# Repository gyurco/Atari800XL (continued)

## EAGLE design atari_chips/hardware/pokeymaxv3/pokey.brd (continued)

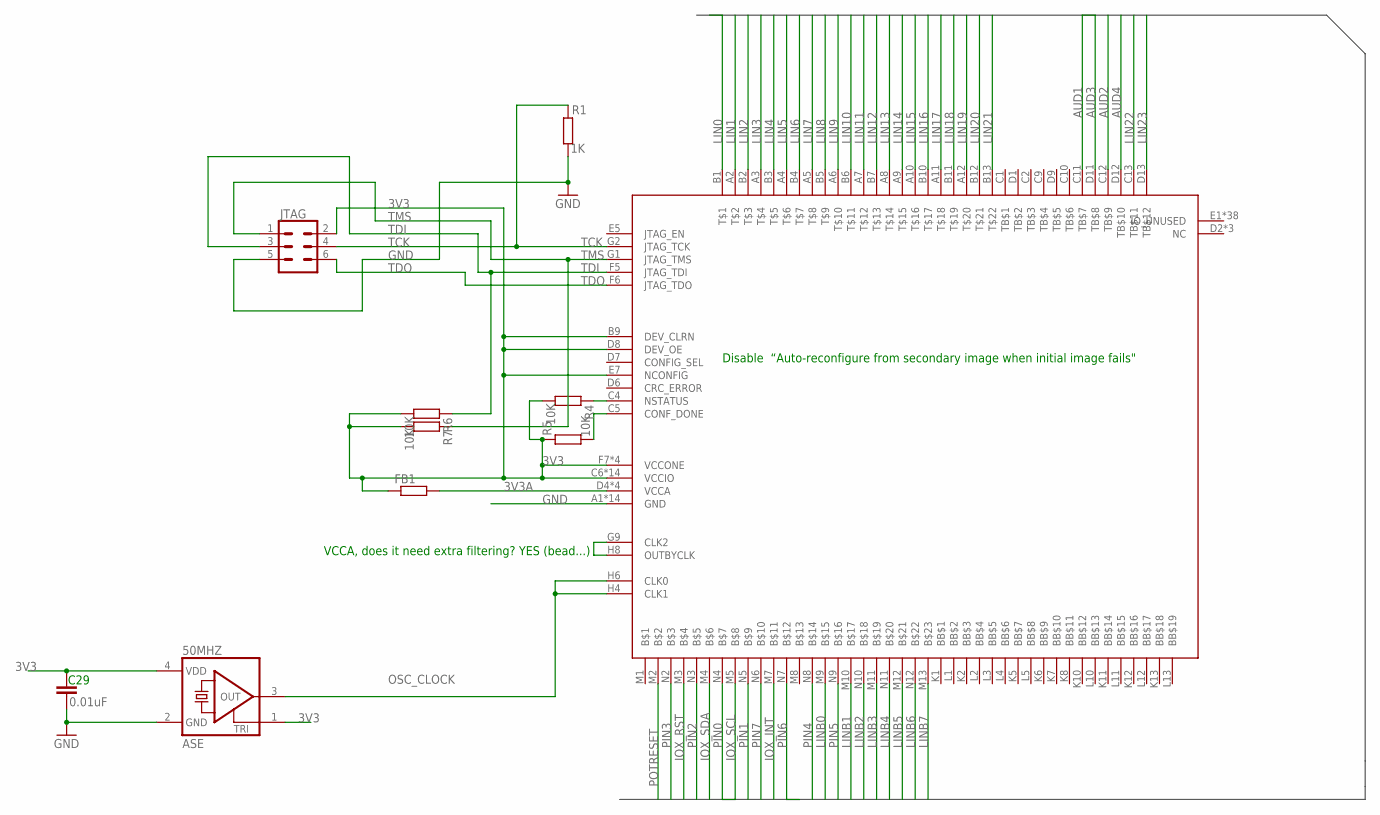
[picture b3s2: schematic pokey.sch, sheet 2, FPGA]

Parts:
50MHZ: ASE
C29: 0.01uF; C0402
FB1: R-EU_R0402; R0402
JTAG: CONN_03X2LOCK; 2X3_LOCK
MAX10: MAX10; U169SMALL
R1: 1K; R0402
R4, R5, R6, R7: 10K; R0402

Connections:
3V3: 50MHZ.1 (TRI), 50MHZ.4 (VDD), C29.1, FB1.1, JTAG.2, MAX10.B9 (DEV_CLRN), MAX10.C6 (VCCIO), MAX10.C7 (VCCIO), MAX10.C8 (VCCIO), MAX10.D8 (DEV_OE), MAX10.E7 (NCONFIG), MAX10.F2 (VCCIO), MAX10.F7 (VCCONE), MAX10.F11 (VCCIO), MAX10.G3 (VCCIO), MAX10.G6 (VCCONE), MAX10.G8 (VCCONE), MAX10.G11 (VCCIO), MAX10.H7 (VCCONE), MAX10.H11 (VCCIO), MAX10.J3 (VCCIO), MAX10.J11 (VCCIO), MAX10.K3 (VCCIO), MAX10.L6 (VCCIO), MAX10.L7 (VCCIO), MAX10.L8 (VCCIO), R4.2, R5.1, R6.2, R7.2; also elsewhere on the board
3V3A: FB1.2, MAX10.D4 (VCCA), MAX10.D10 (VCCA), MAX10.K4 (VCCA), MAX10.K9 (VCCA); also elsewhere on the board
AUD1: MAX10.C11 (TB$7); also elsewhere on the board
AUD2: MAX10.C12 (TB$9); also elsewhere on the board
AUD3: MAX10.D11 (TB$8); also elsewhere on the board
AUD4: MAX10.D12 (TB$10); also elsewhere on the board
CONF_DONE: MAX10.C5 (CONF_DONE), R5.2
FAKE_CLK: MAX10.G9 (CLK2), MAX10.H8 (OUTBYCLK)
GND: 50MHZ.2 (GND), C29.2, JTAG.5, MAX10.A1 (GND), MAX10.A13 (GND), MAX10.B8 (GND), MAX10.C3 (GND), MAX10.D5 (GND), MAX10.E11 (GND), MAX10.F3 (GND), MAX10.G7 (GND), MAX10.H12 (GND), MAX10.J4 (GND), MAX10.L9 (GND), MAX10.M6 (GND), MAX10.N1 (GND), MAX10.N13 (GND), R1.2; also elsewhere on the board
IOX_INT: MAX10.M7; also elsewhere on the board
IOX_RST: MAX10.M3; also elsewhere on the board
IOX_SCL: MAX10.M5; also elsewhere on the board
IOX_SDA: MAX10.M4; also elsewhere on the board
LIN0: MAX10.B1; also elsewhere on the board
LIN1: MAX10.A2; also elsewhere on the board
LIN2: MAX10.B2; also elsewhere on the board
LIN3: MAX10.A3; also elsewhere on the board
LIN4: MAX10.B3; also elsewhere on the board
LIN5: MAX10.A4; also elsewhere on the board
LIN6: MAX10.B4; also elsewhere on the board
LIN7: MAX10.A5; also elsewhere on the board
LIN8: MAX10.B5; also elsewhere on the board
LIN9: MAX10.A6; also elsewhere on the board
LIN10: MAX10.B6; also elsewhere on the board
LIN11: MAX10.A7; also elsewhere on the board
LIN12: MAX10.B7; also elsewhere on the board
LIN13: MAX10.A8; also elsewhere on the board
LIN14: MAX10.A9; also elsewhere on the board
LIN15: MAX10.A10; also elsewhere on the board
LIN16: MAX10.B10; also elsewhere on the board
LIN17: MAX10.A11; also elsewhere on the board
LIN18: MAX10.B11; also elsewhere on the board
LIN19: MAX10.A12; also elsewhere on the board
LIN20: MAX10.B12; also elsewhere on the board
LIN21: MAX10.B13; also elsewhere on the board
LIN22: MAX10.C13 (TB$11); also elsewhere on the board
LIN23: MAX10.D13 (TB$12); also elsewhere on the board
LINB0: MAX10.M9; also elsewhere on the board
LINB1: MAX10.M10; also elsewhere on the board
LINB2: MAX10.N10; also elsewhere on the board
LINB3: MAX10.M11; also elsewhere on the board
LINB4: MAX10.N11; also elsewhere on the board
LINB5: MAX10.M12; also elsewhere on the board
LINB6: MAX10.N12; also elsewhere on the board
LINB7: MAX10.M13; also elsewhere on the board
NSTATUS: MAX10.C4 (NSTATUS), R4.1
OSC_CLOCK: 50MHZ.3 (OUT), MAX10.H4 (CLK1), MAX10.H6 (CLK0)
PIN0: MAX10.N4; also elsewhere on the board
PIN1: MAX10.N5; also elsewhere on the board
PIN2: MAX10.N3; also elsewhere on the board
PIN3: MAX10.N2; also elsewhere on the board
PIN4: MAX10.N8; also elsewhere on the board
PIN5: MAX10.N9; also elsewhere on the board
PIN6: MAX10.N7; also elsewhere on the board
PIN7: MAX10.N6; also elsewhere on the board
POTRESET: MAX10.M2; also elsewhere on the board
TCK: JTAG.4, MAX10.G2 (JTAG_TCK), R1.1
TDI: JTAG.3, MAX10.F5 (JTAG_TDI), R6.1
TDO: JTAG.6, MAX10.F6 (JTAG_TDO)
TMS: JTAG.1, MAX10.G1 (JTAG_TMS), R7.1

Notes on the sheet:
VCCA, does it need extra filtering? YES (bead...)
Disable “Auto-reconfigure from secondary image when initial image fails"

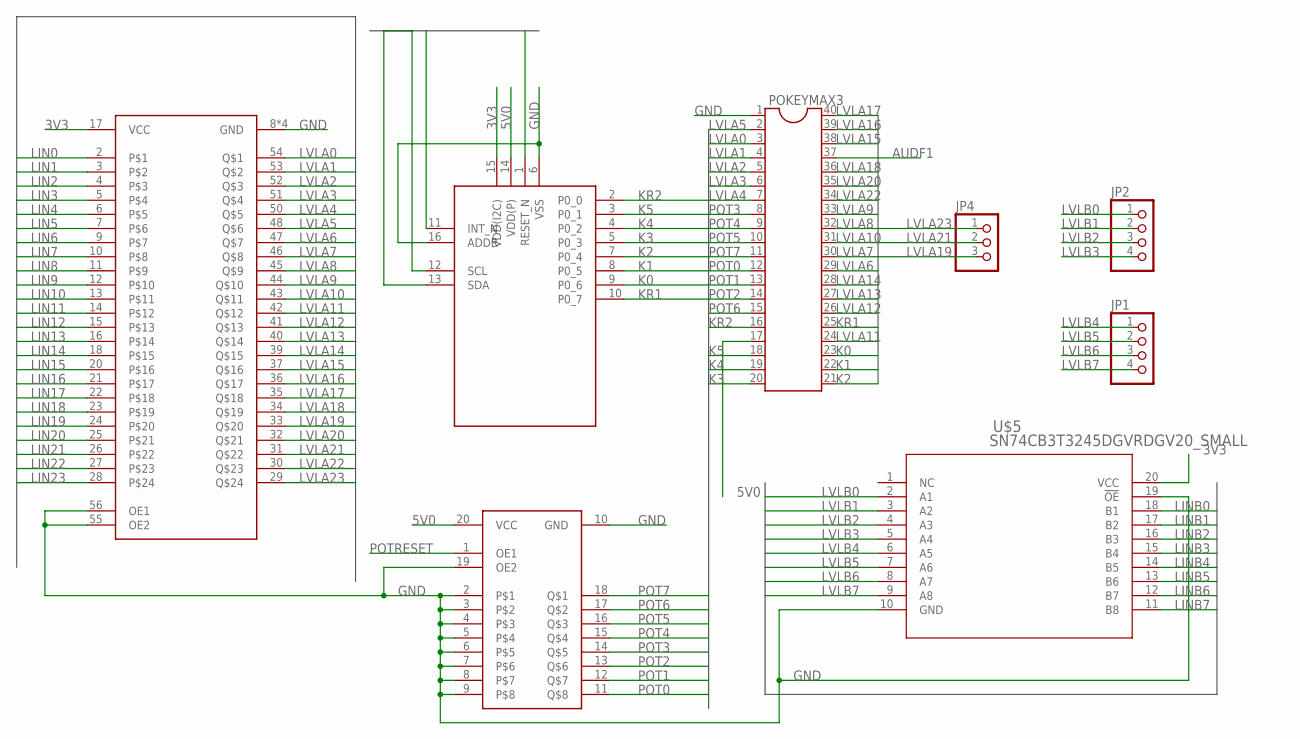
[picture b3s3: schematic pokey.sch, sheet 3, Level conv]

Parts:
JP1, JP2: PINHD-1X4; 1X04
JP4: PINHD-1X3; 1X03
POKEYMAX3: DIL40
U$1: PCAL6408A; XQFN16V2
U$2: SN74CB3T16211SM; 56TVSOP_SMALL
U$4: 74AHCT541ADHVQFN-EP; DHVQFN-EP
U$5: SN74CB3T3245DGVRDGV20_SMALL; DGV20_SMALL

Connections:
3V3: U$1.15 (VDD(I2C)), U$2.17 (VCC), U$5.20 (VCC); also elsewhere on the board
5V0: POKEYMAX3.17, U$1.14 (VDD(P)), U$4.20 (VCC); also elsewhere on the board
AUDF1: POKEYMAX3.37; also elsewhere on the board
GND: POKEYMAX3.1, U$1.6 (VSS), U$1.16 (ADDR), U$2.8 (GND), U$2.19 (GND), U$2.38 (GND), U$2.49 (GND), U$2.55 (OE2), U$2.56 (OE1), U$4.2, U$4.3, U$4.4, U$4.5, U$4.6, U$4.7, U$4.8, U$4.9, U$4.10 (GND), U$4.19 (OE2), U$5.10 (GND), U$5.19 (!OE); also elsewhere on the board
IOX_INT: U$1.11 (INT_N); also elsewhere on the board
IOX_RST: U$1.1 (RESET_N); also elsewhere on the board
IOX_SCL: U$1.12 (SCL); also elsewhere on the board
IOX_SDA: U$1.13 (SDA); also elsewhere on the board
K0: POKEYMAX3.23, U$1.9 (P0_6)
K1: POKEYMAX3.22, U$1.8 (P0_5)
K2: POKEYMAX3.21, U$1.7 (P0_4)
K3: POKEYMAX3.20, U$1.5 (P0_3)
K4: POKEYMAX3.19, U$1.4 (P0_2)
K5: POKEYMAX3.18, U$1.3 (P0_1)
KR1: POKEYMAX3.25, U$1.10 (P0_7)
KR2: POKEYMAX3.16, U$1.2 (P0_0)
LIN0: U$2.2; also elsewhere on the board
LIN1: U$2.3; also elsewhere on the board
LIN2: U$2.4; also elsewhere on the board
LIN3: U$2.5; also elsewhere on the board
LIN4: U$2.6; also elsewhere on the board
LIN5: U$2.7; also elsewhere on the board
LIN6: U$2.9; also elsewhere on the board
LIN7: U$2.10; also elsewhere on the board
LIN8: U$2.11; also elsewhere on the board
LIN9: U$2.12; also elsewhere on the board
LIN10: U$2.13; also elsewhere on the board
LIN11: U$2.14; also elsewhere on the board
LIN12: U$2.15; also elsewhere on the board
LIN13: U$2.16; also elsewhere on the board
LIN14: U$2.18; also elsewhere on the board
LIN15: U$2.20; also elsewhere on the board
LIN16: U$2.21; also elsewhere on the board
LIN17: U$2.22; also elsewhere on the board
LIN18: U$2.23; also elsewhere on the board
LIN19: U$2.24; also elsewhere on the board
LIN20: U$2.25; also elsewhere on the board
LIN21: U$2.26; also elsewhere on the board
LIN22: U$2.27; also elsewhere on the board
LIN23: U$2.28; also elsewhere on the board
LINB0: U$5.18 (B1); also elsewhere on the board
LINB1: U$5.17 (B2); also elsewhere on the board
LINB2: U$5.16 (B3); also elsewhere on the board
LINB3: U$5.15 (B4); also elsewhere on the board
LINB4: U$5.14 (B5); also elsewhere on the board
LINB5: U$5.13 (B6); also elsewhere on the board
LINB6: U$5.12 (B7); also elsewhere on the board
LINB7: U$5.11 (B8); also elsewhere on the board
LVLA0: POKEYMAX3.3, U$2.54
LVLA1: POKEYMAX3.4, U$2.53
LVLA2: POKEYMAX3.5, U$2.52
LVLA3: POKEYMAX3.6, U$2.51
LVLA4: POKEYMAX3.7, U$2.50
LVLA5: POKEYMAX3.2, U$2.48
LVLA6: POKEYMAX3.29, U$2.47
LVLA7: POKEYMAX3.30, U$2.46
LVLA8: POKEYMAX3.32, U$2.45
LVLA9: POKEYMAX3.33, U$2.44
LVLA10: POKEYMAX3.31, U$2.43
LVLA11: POKEYMAX3.24, U$2.42
LVLA12: POKEYMAX3.26, U$2.41
LVLA13: POKEYMAX3.27, U$2.40
LVLA14: POKEYMAX3.28, U$2.39
LVLA15: POKEYMAX3.38, U$2.37
LVLA16: POKEYMAX3.39, U$2.36
LVLA17: POKEYMAX3.40, U$2.35
LVLA18: POKEYMAX3.36, U$2.34
LVLA19: JP4.3, U$2.33
LVLA20: POKEYMAX3.35, U$2.32
LVLA21: JP4.2, U$2.31
LVLA22: POKEYMAX3.34, U$2.30
LVLA23: JP4.1, U$2.29
LVLB0: JP2.1, U$5.2 (A1)
LVLB1: JP2.2, U$5.3 (A2)
LVLB2: JP2.3, U$5.4 (A3)
LVLB3: JP2.4, U$5.5 (A4)
LVLB4: JP1.1, U$5.6 (A5)
LVLB5: JP1.2, U$5.7 (A6)
LVLB6: JP1.3, U$5.8 (A7)
LVLB7: JP1.4, U$5.9 (A8)
POT0: POKEYMAX3.12, U$4.11; also elsewhere on the board
POT1: POKEYMAX3.13, U$4.12; also elsewhere on the board
POT2: POKEYMAX3.14, U$4.13; also elsewhere on the board
POT3: POKEYMAX3.8, U$4.14; also elsewhere on the board
POT4: POKEYMAX3.9, U$4.15; also elsewhere on the board
POT5: POKEYMAX3.10, U$4.16; also elsewhere on the board
POT6: POKEYMAX3.15, U$4.17; also elsewhere on the board
POT7: POKEYMAX3.11, U$4.18; also elsewhere on the board
POTRESET: U$4.1 (OE1); also elsewhere on the board

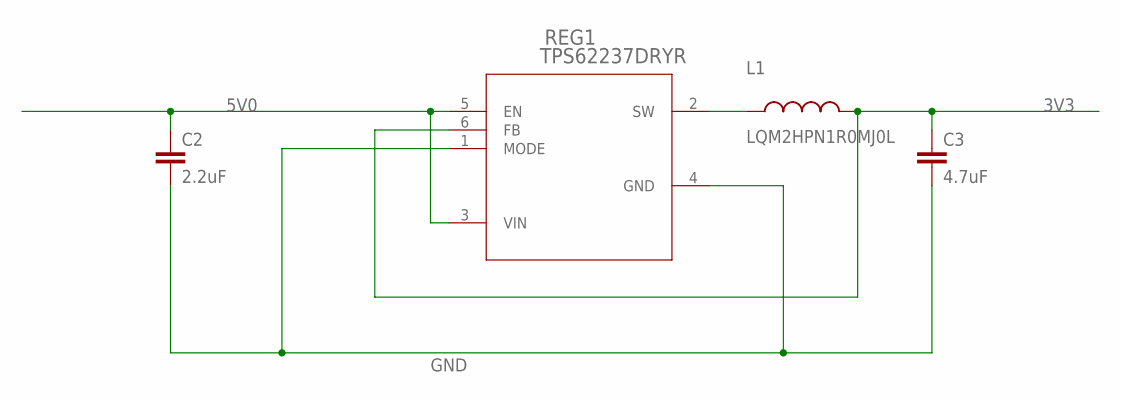
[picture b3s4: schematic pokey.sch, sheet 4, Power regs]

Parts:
C2: 2.2uF; C0402
C3: 4.7uF; C0402
L1: LQM2HPN1R0MJ0L; INDC1008X04
REG1: TPS62237DRYR; DRY6

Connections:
3V3: C3.1, L1.2, REG1.6 (FB); also elsewhere on the board
5V0: C2.1, REG1.3 (VIN), REG1.5 (EN); also elsewhere on the board
GND: C2.2, C3.2, REG1.1 (MODE), REG1.4 (GND); also elsewhere on the board
unnamed: L1.1, REG1.2 (SW)

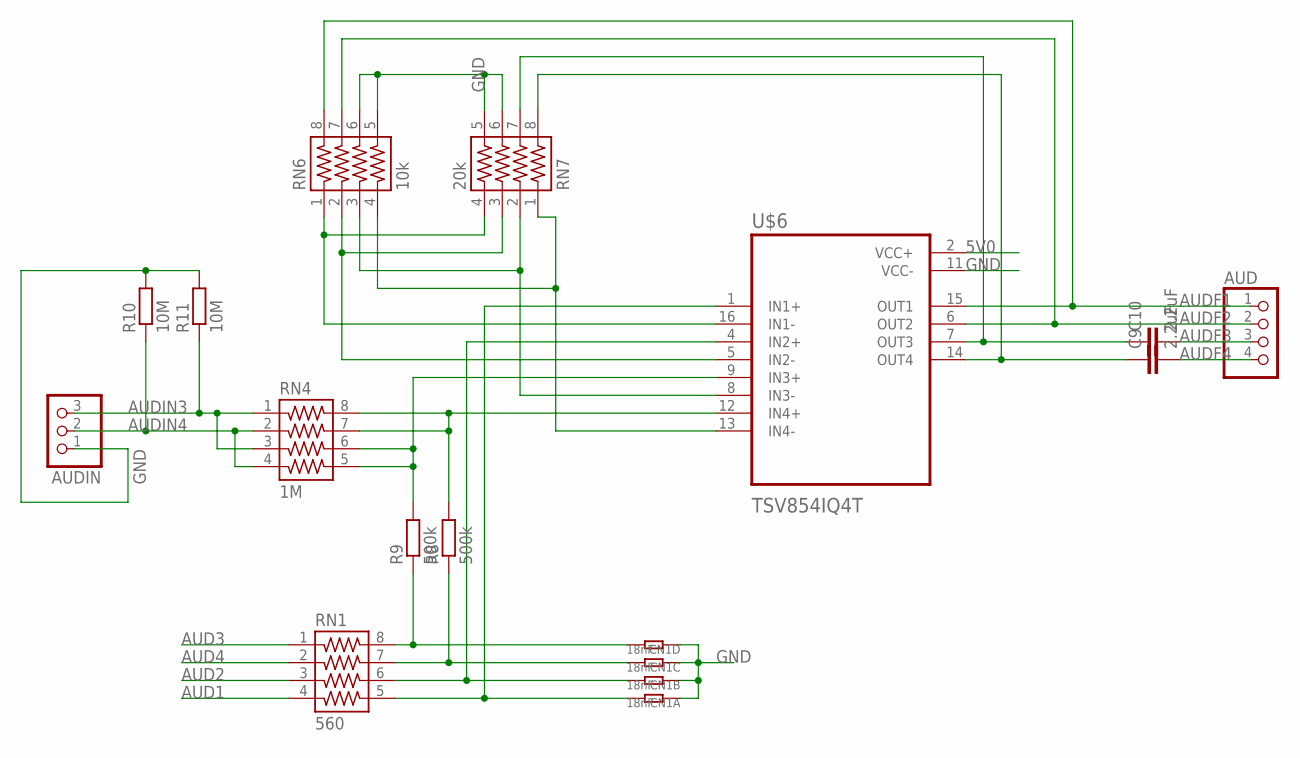
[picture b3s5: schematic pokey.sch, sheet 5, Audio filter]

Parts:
AUD: PINHD-1X4; 1X04
AUDIN: PINHD-1X3; 1X03
C9, C10: 2.2uF; C0402
CN1: 18nF; R1206-8
R8, R9: 500k; R0402
R10, R11: 10M; R0402
RN1: 560; 742-8
RN4: 1M; 742-8
RN6: 10k; 742-8
RN7: 20k; 742-8
U$6: TSV854IQ4T; QFN50P300X300X100-16N

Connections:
5V0: U$6.2 (VCC+); also elsewhere on the board
AMPIN1M: RN6.1, RN7.4, U$6.16 (IN1-)
AMPIN1P: CN1.8 (2), RN1.5, U$6.1 (IN1+)
AMPIN2M: RN6.2, RN7.3, U$6.5 (IN2-)
AMPIN2P: CN1.7 (2), RN1.6, U$6.4 (IN2+)
AMPIN3M: RN6.3, RN7.2, U$6.8 (IN3-)
AMPIN3P: R9.2, RN4.5, RN4.6, U$6.9 (IN3+)
AMPIN4P: R8.2, RN4.7, RN4.8, U$6.12 (IN4+)
AUD1: RN1.4; also elsewhere on the board
AUD2: RN1.3; also elsewhere on the board
AUD3: RN1.1; also elsewhere on the board
AUD4: RN1.2; also elsewhere on the board
AUDF1: AUD.1, RN6.8, U$6.15 (OUT1); also elsewhere on the board
AUDF2: AUD.2, RN6.7, U$6.6 (OUT2)
AUDF3: AUD.3, C10.2
AUDF4: AUD.4, C9.2
AUDIN3: AUDIN.3, R11.1, RN4.1, RN4.3
AUDIN4: AUDIN.2, R10.1, RN4.2, RN4.4
GND: AUDIN.1, CN1.1, CN1.2 (1), CN1.3 (1), CN1.4 (1), R10.2, R11.2, RN6.5, RN6.6, RN7.5, RN7.6, U$6.11 (VCC-); also elsewhere on the board
unnamed: CN1.5 (2), R9.1, RN1.8
unnamed: CN1.6 (2), R8.1, RN1.7
unnamed: C9.1, RN7.8, U$6.14 (OUT4)
unnamed: C10.1, RN7.7, U$6.7 (OUT3)
unnamed: RN6.4, RN7.1, U$6.13 (IN4-)

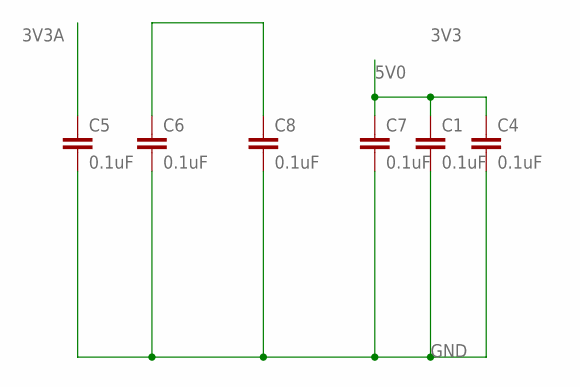
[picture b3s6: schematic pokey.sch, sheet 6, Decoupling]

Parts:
C1, C4, C5, C6, C7, C8: 0.1uF; C0402

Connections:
3V3: C6.1, C8.1; also elsewhere on the board
3V3A: C5.1; also elsewhere on the board
5V0: C1.1, C4.1, C7.1; also elsewhere on the board
GND: C1.2, C4.2, C5.2, C6.2, C7.2, C8.2; also elsewhere on the board

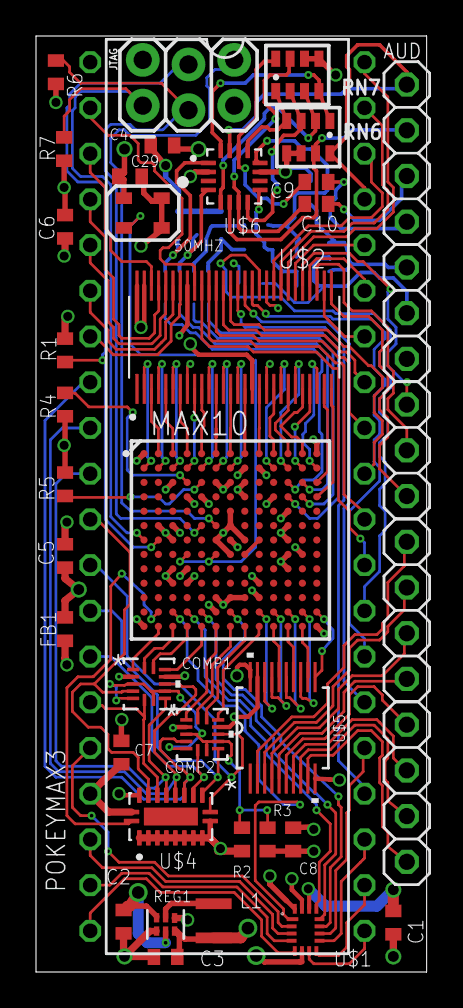
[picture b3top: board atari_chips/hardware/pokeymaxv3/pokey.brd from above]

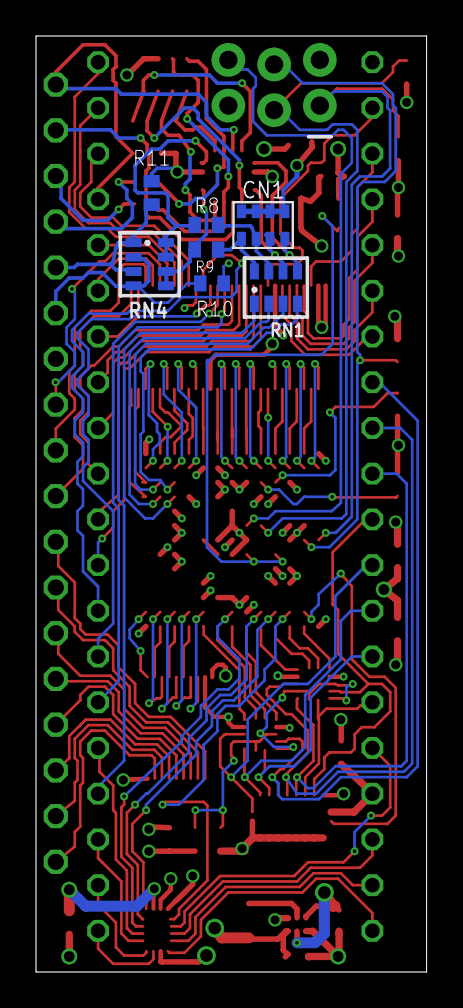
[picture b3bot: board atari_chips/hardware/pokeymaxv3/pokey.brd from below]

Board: 4 copper layers, 21.7 x 52.0 mm, 46 parts (7 on the bottom side), 129 nets.

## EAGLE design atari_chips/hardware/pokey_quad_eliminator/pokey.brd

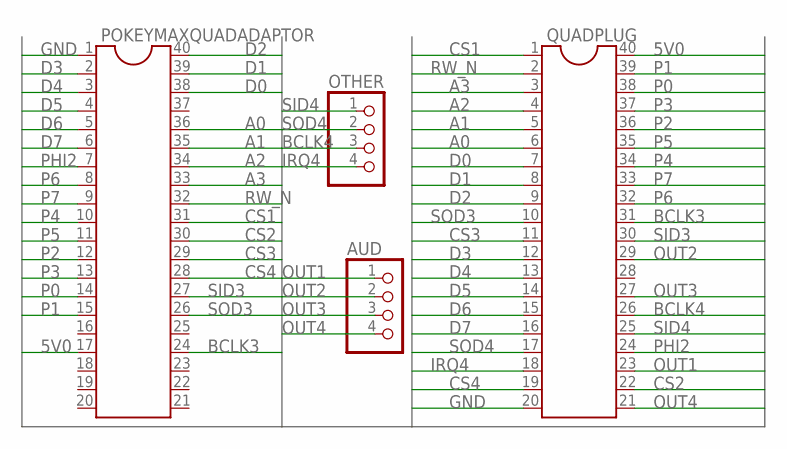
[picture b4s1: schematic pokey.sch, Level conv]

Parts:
AUD: PINHD-1X4; 1X04
OTHER: PINHD-1X4; 1X04
POKEYMAXQUADADAPTOR: DIL40
QUADPLUG: DIL40

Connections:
5V0: POKEYMAXQUADADAPTOR.17, QUADPLUG.40
A0: POKEYMAXQUADADAPTOR.36, QUADPLUG.6
A1: POKEYMAXQUADADAPTOR.35, QUADPLUG.5
A2: POKEYMAXQUADADAPTOR.34, QUADPLUG.4
A3: POKEYMAXQUADADAPTOR.33, QUADPLUG.3
BCLK3: POKEYMAXQUADADAPTOR.24, QUADPLUG.31
BCLK4: OTHER.3, QUADPLUG.26
CS1: POKEYMAXQUADADAPTOR.31, QUADPLUG.1
CS2: POKEYMAXQUADADAPTOR.30, QUADPLUG.22
CS3: POKEYMAXQUADADAPTOR.29, QUADPLUG.11
CS4: POKEYMAXQUADADAPTOR.28, QUADPLUG.19
D0: POKEYMAXQUADADAPTOR.38, QUADPLUG.7
D1: POKEYMAXQUADADAPTOR.39, QUADPLUG.8
D2: POKEYMAXQUADADAPTOR.40, QUADPLUG.9
D3: POKEYMAXQUADADAPTOR.2, QUADPLUG.12
D4: POKEYMAXQUADADAPTOR.3, QUADPLUG.13
D5: POKEYMAXQUADADAPTOR.4, QUADPLUG.14
D6: POKEYMAXQUADADAPTOR.5, QUADPLUG.15
D7: POKEYMAXQUADADAPTOR.6, QUADPLUG.16
GND: POKEYMAXQUADADAPTOR.1, QUADPLUG.20
IRQ4: OTHER.4, QUADPLUG.18
OUT1: AUD.1, QUADPLUG.23
OUT2: AUD.2, QUADPLUG.29
OUT3: AUD.3, QUADPLUG.27
OUT4: AUD.4, QUADPLUG.21
P0: POKEYMAXQUADADAPTOR.14, QUADPLUG.38
P1: POKEYMAXQUADADAPTOR.15, QUADPLUG.39
P2: POKEYMAXQUADADAPTOR.12, QUADPLUG.36
P3: POKEYMAXQUADADAPTOR.13, QUADPLUG.37
P4: POKEYMAXQUADADAPTOR.10, QUADPLUG.34
P5: POKEYMAXQUADADAPTOR.11, QUADPLUG.35
P6: POKEYMAXQUADADAPTOR.8, QUADPLUG.32
P7: POKEYMAXQUADADAPTOR.9, QUADPLUG.33
PHI2: POKEYMAXQUADADAPTOR.7, QUADPLUG.24
RW_N: POKEYMAXQUADADAPTOR.32, QUADPLUG.2
SID3: POKEYMAXQUADADAPTOR.27, QUADPLUG.30
SID4: OTHER.1, QUADPLUG.25
SOD3: POKEYMAXQUADADAPTOR.26, QUADPLUG.10
SOD4: OTHER.2, QUADPLUG.17

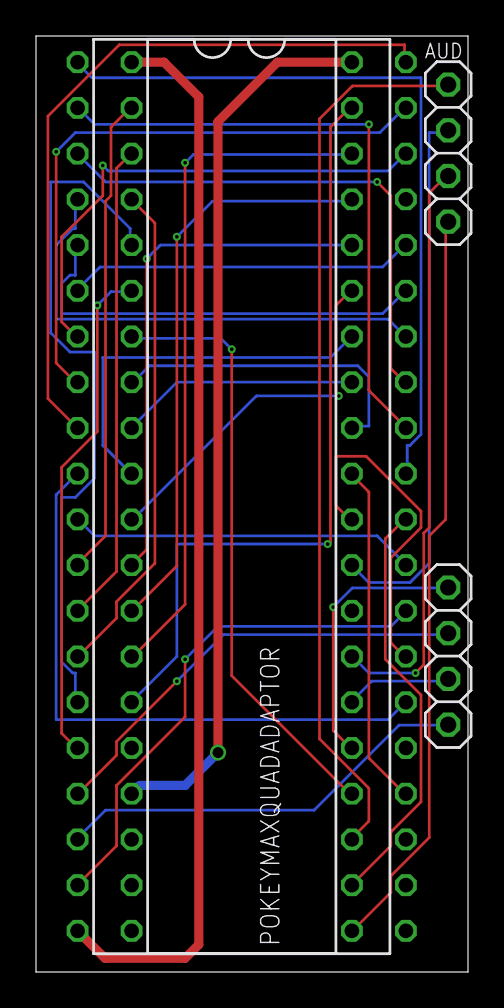
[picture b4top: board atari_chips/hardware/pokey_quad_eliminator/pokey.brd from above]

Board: 2 copper layers, 24.0 x 52.0 mm, 4 parts (0 on the bottom side), 39 nets.

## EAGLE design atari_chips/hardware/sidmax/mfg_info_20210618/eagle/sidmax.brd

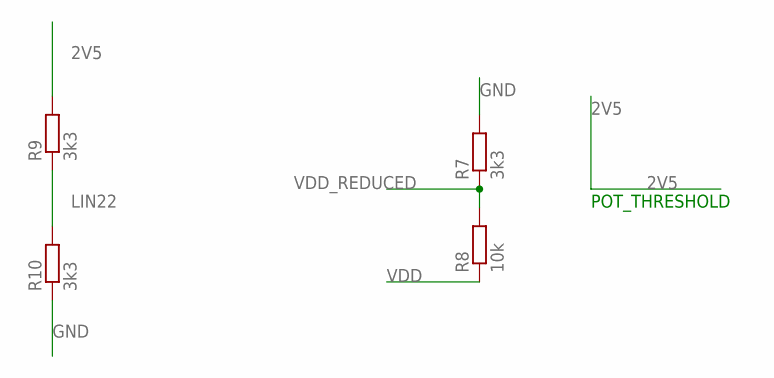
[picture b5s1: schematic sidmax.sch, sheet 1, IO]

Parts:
R7, R9, R10: 3k3; R0402
R8: 10k; R0402

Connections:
2V5: R9.2; also elsewhere on the board
GND: R7.2, R10.1; also elsewhere on the board
LIN22: R9.1, R10.2; also elsewhere on the board
VDD: R8.1; also elsewhere on the board
VDD_REDUCED: R7.1, R8.2; also elsewhere on the board

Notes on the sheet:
POT_THRESHOLD

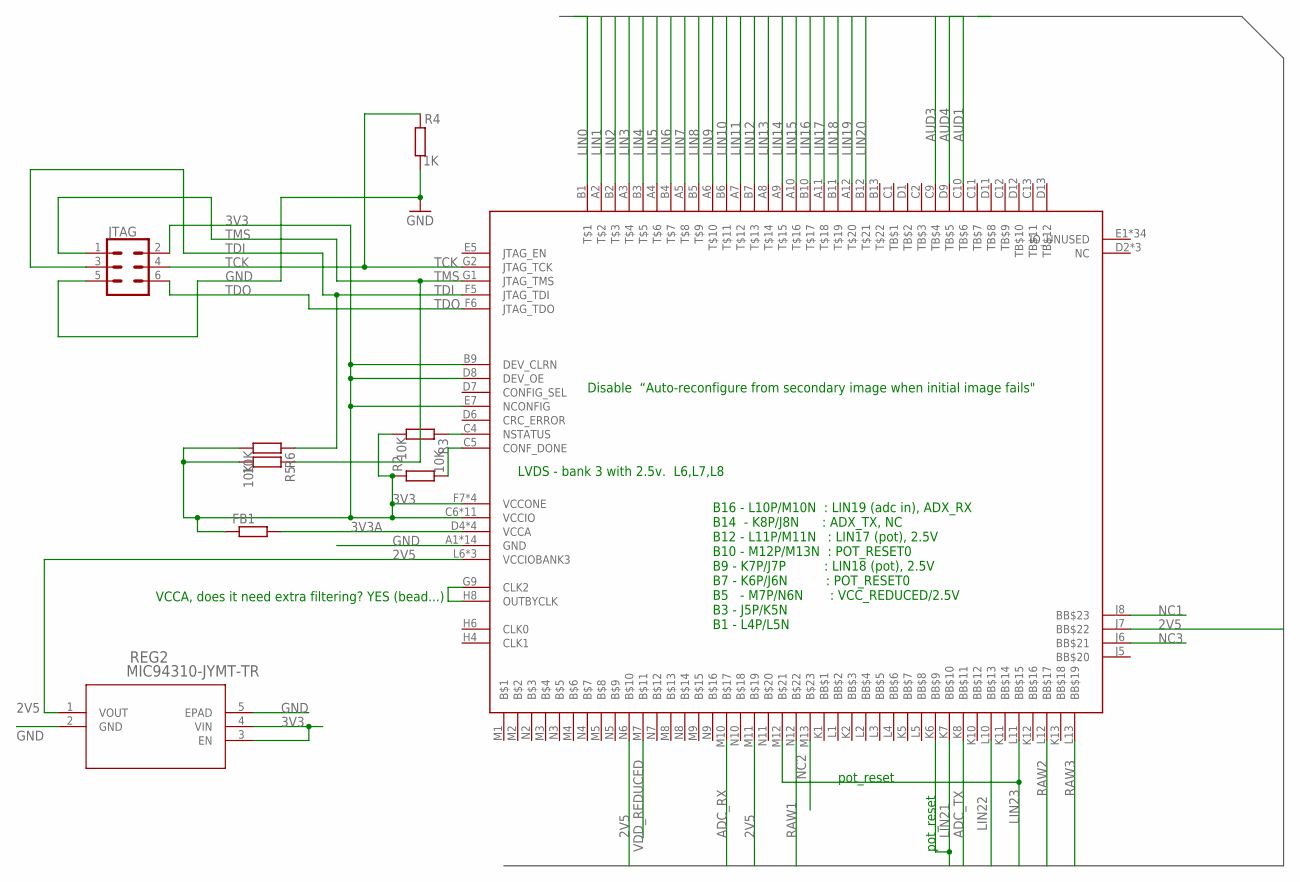
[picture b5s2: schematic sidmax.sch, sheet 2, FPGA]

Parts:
FB1: R-EU_R0402; R0402
JTAG: CONN_03X2LOCK; 2X3_LOCK
R2, R3, R5, R6: 10K; R0402
R4: 1K; R0402
REG2: MIC94310-JYMT-TR; TDFN4_1P2X1P6_MCH
U3: MAX10; U169SMALL

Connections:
2V5: REG2.1 (VOUT), U3.J7 (BB$22), U3.L6 (VCCIOBANK3), U3.L7 (VCCIOBANK3), U3.L8 (VCCIOBANK3), U3.M11, U3.N6; also elsewhere on the board
3V3: FB1.1, JTAG.2, R2.1, R3.2, R5.2, R6.2, REG2.3 (EN), REG2.4 (VIN), U3.B9 (DEV_CLRN), U3.C6 (VCCIO), U3.C7 (VCCIO), U3.C8 (VCCIO), U3.D8 (DEV_OE), U3.E7 (NCONFIG), U3.F2 (VCCIO), U3.F7 (VCCONE), U3.F11 (VCCIO), U3.G3 (VCCIO), U3.G6 (VCCONE), U3.G8 (VCCONE), U3.G11 (VCCIO), U3.H7 (VCCONE), U3.H11 (VCCIO), U3.J3 (VCCIO), U3.J11 (VCCIO), U3.K3 (VCCIO); also elsewhere on the board
3V3A: FB1.2, U3.D4 (VCCA), U3.D10 (VCCA), U3.K4 (VCCA), U3.K9 (VCCA); also elsewhere on the board
ADC_RX: U3.M10; also elsewhere on the board
ADC_TX: U3.K8 (BB$11); also elsewhere on the board
AUD1: U3.C10 (TB$6); also elsewhere on the board
AUD3: U3.C9 (TB$4); also elsewhere on the board
AUD4: U3.D9 (TB$5); also elsewhere on the board
CONF_DONE: R2.2, U3.C5 (CONF_DONE)
FAKE_CLK: U3.G9 (CLK2), U3.H8 (OUTBYCLK)
GND: JTAG.5, R4.2, REG2.2 (GND), REG2.5 (EPAD), U3.A1 (GND), U3.A13 (GND), U3.B8 (GND), U3.C3 (GND), U3.D5 (GND), U3.E11 (GND), U3.F3 (GND), U3.G7 (GND), U3.H12 (GND), U3.J4 (GND), U3.L9 (GND), U3.M6 (GND), U3.N1 (GND), U3.N13 (GND); also elsewhere on the board
LIN0: U3.B1; also elsewhere on the board
LIN1: U3.A2; also elsewhere on the board
LIN2: U3.B2; also elsewhere on the board
LIN3: U3.A3; also elsewhere on the board
LIN4: U3.B3; also elsewhere on the board
LIN5: U3.A4; also elsewhere on the board
LIN6: U3.B4; also elsewhere on the board
LIN7: U3.A5; also elsewhere on the board
LIN8: U3.B5; also elsewhere on the board
LIN9: U3.A6; also elsewhere on the board
LIN10: U3.B6; also elsewhere on the board
LIN11: U3.A7; also elsewhere on the board
LIN12: U3.B7; also elsewhere on the board
LIN13: U3.A8; also elsewhere on the board
LIN14: U3.A9; also elsewhere on the board
LIN15: U3.A10; also elsewhere on the board
LIN16: U3.B10; also elsewhere on the board
LIN17: U3.A11; also elsewhere on the board
LIN18: U3.B11; also elsewhere on the board
LIN19: U3.A12; also elsewhere on the board
LIN20: U3.B12; also elsewhere on the board
LIN21: U3.K6 (BB$9), U3.K7 (BB$10); also elsewhere on the board
LIN22: U3.L10 (BB$13); also elsewhere on the board
LIN23: U3.L11 (BB$15), U3.M12; also elsewhere on the board
NC1: U3.J8 (BB$23)
NC2: U3.M13
NC3: U3.J6 (BB$21)
NSTATUS: R3.1, U3.C4 (NSTATUS)
RAW1: U3.N12; also elsewhere on the board
RAW2: U3.L12 (BB$17); also elsewhere on the board
RAW3: U3.L13 (BB$19); also elsewhere on the board
TCK: JTAG.4, R4.1, U3.G2 (JTAG_TCK)
TDI: JTAG.3, R6.1, U3.F5 (JTAG_TDI)
TDO: JTAG.6, U3.F6 (JTAG_TDO)
TMS: JTAG.1, R5.1, U3.G1 (JTAG_TMS)
VDD_REDUCED: U3.M7; also elsewhere on the board

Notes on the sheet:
VCCA, does it need extra filtering? YES (bead...)
Disable “Auto-reconfigure from secondary image when initial image fails"
LVDS - bank 3 with 2.5v. L6,L7,L8
B16 - L10P/M10N : LIN19 (adc in), ADX_RX B14 - K8P/J8N : ADX_TX, NC B12 - L11P/M11N : LIN17 (pot), 2.5V B10 - M12P/M13N : POT_RESET0 B9 - K7P/J7P : LIN18 (pot), 2.5V B7 - K6P/J6N : POT_RESET0 B5 - M7P/N6N : VCC_REDUCED/2.5V B3 - J5P/K5N B1 - L4P/L5N
pot_reset

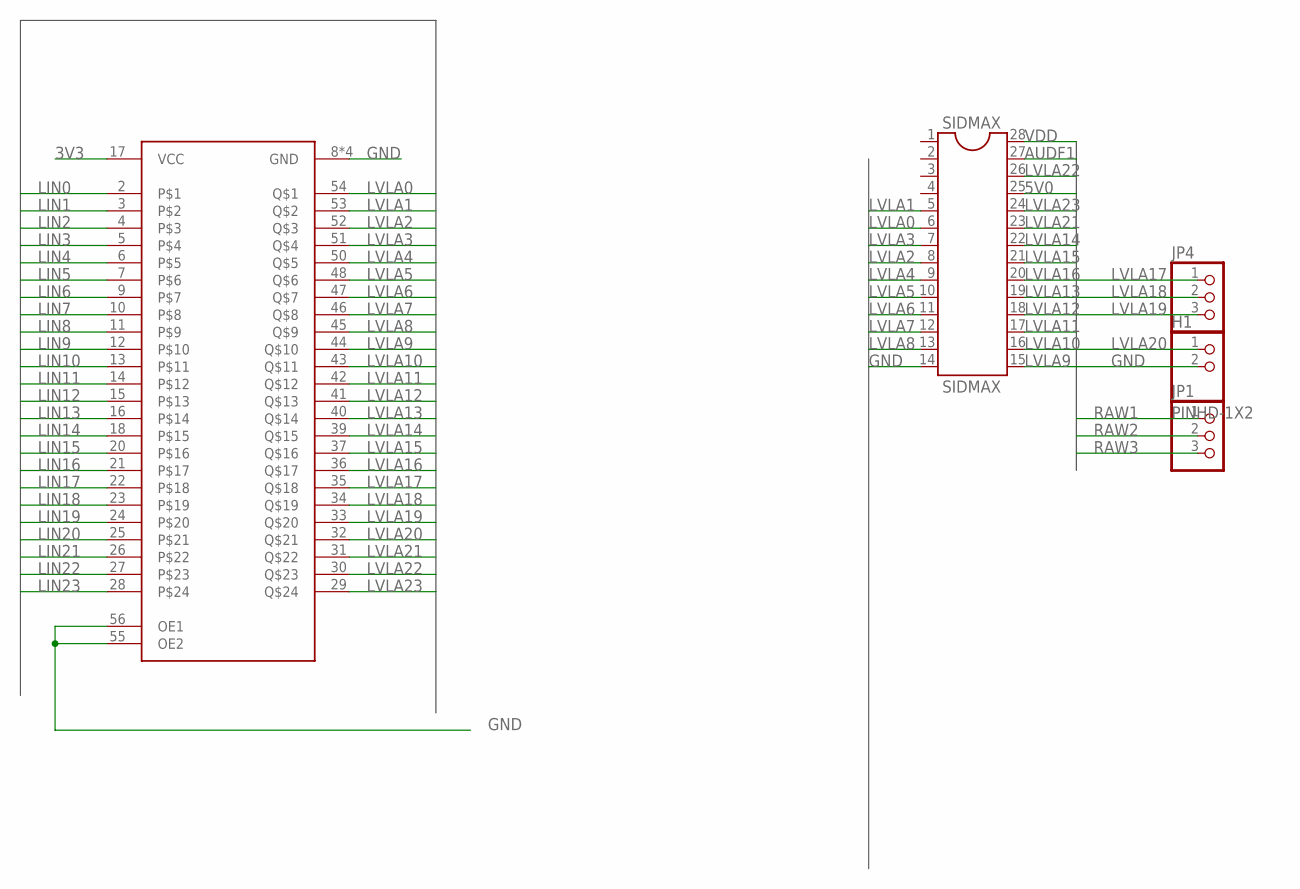
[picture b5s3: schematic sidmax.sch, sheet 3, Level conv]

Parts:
H1: PINHD-1X2; 1X02
JP1, JP4: PINHD-1X3; 1X03
SIDMAX: SIDMAX; DIL28-6
U2: SN74CB3T16211SM; 56TVSOP_SMALL

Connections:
3V3: U2.17 (VCC); also elsewhere on the board
5V0: SIDMAX.25; also elsewhere on the board
AUDF1: SIDMAX.27; also elsewhere on the board
GND: H1.2, SIDMAX.14, U2.8 (GND), U2.19 (GND), U2.38 (GND), U2.49 (GND), U2.55 (OE2), U2.56 (OE1); also elsewhere on the board
LIN0: U2.2; also elsewhere on the board
LIN1: U2.3; also elsewhere on the board
LIN2: U2.4; also elsewhere on the board
LIN3: U2.5; also elsewhere on the board
LIN4: U2.6; also elsewhere on the board
LIN5: U2.7; also elsewhere on the board
LIN6: U2.9; also elsewhere on the board
LIN7: U2.10; also elsewhere on the board
LIN8: U2.11; also elsewhere on the board
LIN9: U2.12; also elsewhere on the board
LIN10: U2.13; also elsewhere on the board
LIN11: U2.14; also elsewhere on the board
LIN12: U2.15; also elsewhere on the board
LIN13: U2.16; also elsewhere on the board
LIN14: U2.18; also elsewhere on the board
LIN15: U2.20; also elsewhere on the board
LIN16: U2.21; also elsewhere on the board
LIN17: U2.22; also elsewhere on the board
LIN18: U2.23; also elsewhere on the board
LIN19: U2.24; also elsewhere on the board
LIN20: U2.25; also elsewhere on the board
LIN21: U2.26; also elsewhere on the board
LIN22: U2.27; also elsewhere on the board
LIN23: U2.28; also elsewhere on the board
LVLA0: SIDMAX.6, U2.54
LVLA1: SIDMAX.5, U2.53
LVLA2: SIDMAX.8, U2.52
LVLA3: SIDMAX.7, U2.51
LVLA4: SIDMAX.9, U2.50
LVLA5: SIDMAX.10, U2.48
LVLA6: SIDMAX.11, U2.47
LVLA7: SIDMAX.12, U2.46
LVLA8: SIDMAX.13, U2.45
LVLA9: SIDMAX.15, U2.44
LVLA10: SIDMAX.16, U2.43
LVLA11: SIDMAX.17, U2.42
LVLA12: SIDMAX.18, U2.41
LVLA13: SIDMAX.19, U2.40
LVLA14: SIDMAX.22, U2.39
LVLA15: SIDMAX.21, U2.37
LVLA16: SIDMAX.20, U2.36
LVLA17: JP4.1, U2.35
LVLA18: JP4.2, U2.34
LVLA19: JP4.3, U2.33
LVLA20: H1.1, U2.32
LVLA21: SIDMAX.23, U2.31
LVLA22: SIDMAX.26, U2.30
LVLA23: SIDMAX.24, U2.29
RAW1: JP1.1; also elsewhere on the board
RAW2: JP1.2; also elsewhere on the board
RAW3: JP1.3; also elsewhere on the board
VDD: SIDMAX.28; also elsewhere on the board

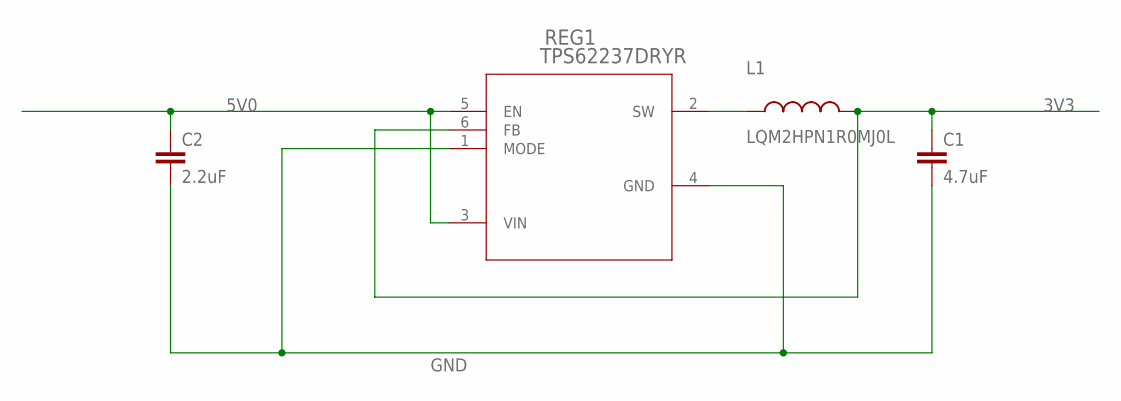
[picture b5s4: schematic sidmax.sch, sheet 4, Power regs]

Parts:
C1: 4.7uF; C0402
C2: 2.2uF; C0402
L1: LQM2HPN1R0MJ0L; INDC1008X04
REG1: TPS62237DRYR; DRY6

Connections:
3V3: C1.1, L1.2, REG1.6 (FB); also elsewhere on the board
5V0: C2.1, REG1.3 (VIN), REG1.5 (EN); also elsewhere on the board
GND: C1.2, C2.2, REG1.1 (MODE), REG1.4 (GND); also elsewhere on the board
unnamed: L1.1, REG1.2 (SW)

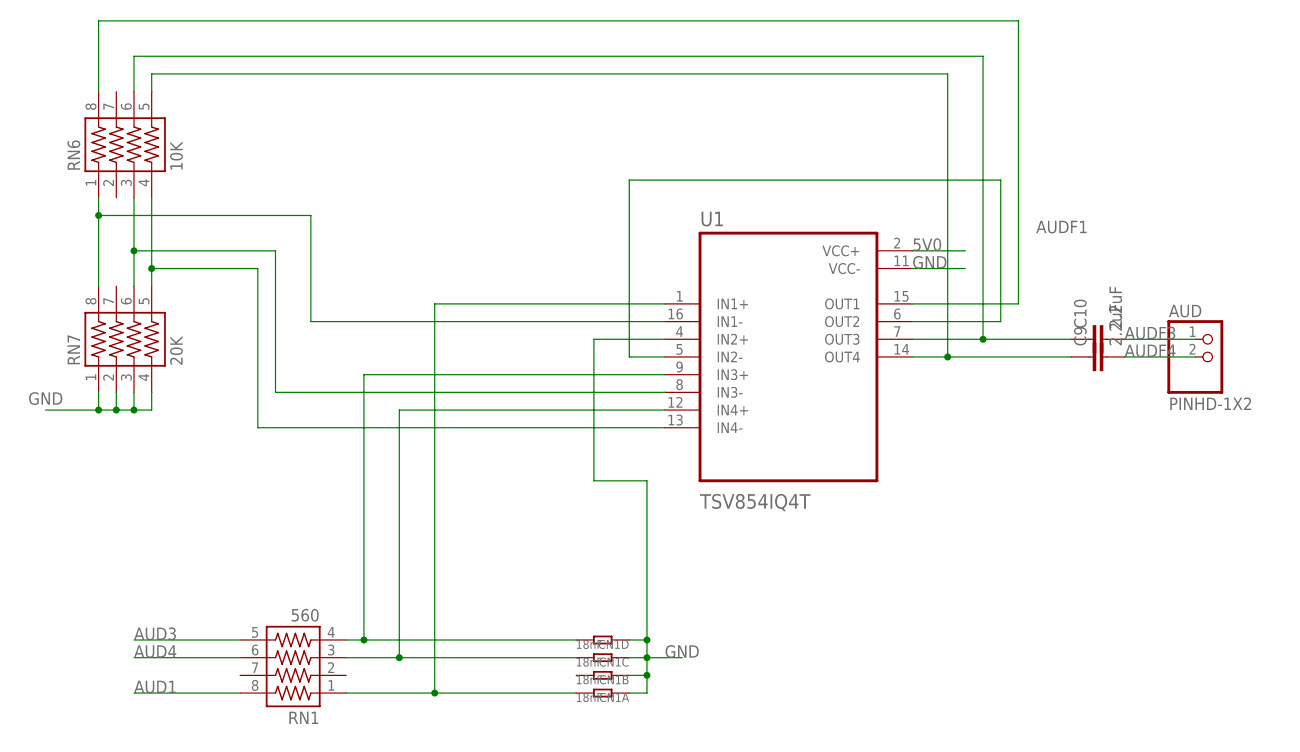
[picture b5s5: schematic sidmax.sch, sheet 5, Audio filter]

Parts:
AUD: PINHD-1X2; 1X02
C9, C10: 2.2uF; C0402
CN1: 18nF; R1206-8
RN1: 560; 741-8
RN6: 10K; 741-8
RN7: 20K; 741-8
U1: TSV854IQ4T; QFN50P300X300X100-16N

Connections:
5V0: U1.2 (VCC+); also elsewhere on the board
AMPIN1M: RN6.1, RN7.8, U1.16 (IN1-)
AMPIN1P: CN1.8 (2), RN1.1, U1.1 (IN1+)
AMPIN3M: RN6.3, RN7.6, U1.8 (IN3-)
AMPIN3P: CN1.5 (2), RN1.4, U1.9 (IN3+)
AMPIN4P: CN1.6 (2), RN1.3, U1.12 (IN4+)
AUD1: RN1.8; also elsewhere on the board
AUD3: RN1.5; also elsewhere on the board
AUD4: RN1.6; also elsewhere on the board
AUDF1: RN6.8, U1.15 (OUT1); also elsewhere on the board
AUDF2: U1.5 (IN2-), U1.6 (OUT2)
AUDF3: AUD.1, C10.2
AUDF4: AUD.2, C9.2
GND: CN1.1, CN1.2 (1), CN1.3 (1), CN1.4 (1), RN7.1, RN7.2, RN7.3, RN7.4, U1.4 (IN2+), U1.11 (VCC-); also elsewhere on the board
unnamed: C9.1, RN6.5, U1.14 (OUT4)
unnamed: C10.1, RN6.6, U1.7 (OUT3)
unnamed: RN6.4, RN7.5, U1.13 (IN4-)

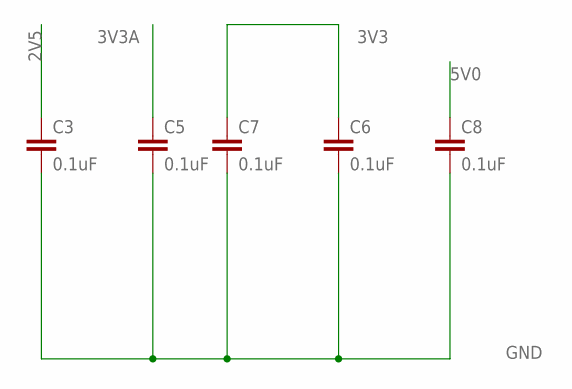
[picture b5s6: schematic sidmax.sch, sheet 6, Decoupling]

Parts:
C3, C5, C6, C7, C8: 0.1uF; C0402

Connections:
2V5: C3.1; also elsewhere on the board
3V3: C6.1, C7.1; also elsewhere on the board
3V3A: C5.1; also elsewhere on the board
5V0: C8.1; also elsewhere on the board
GND: C3.2, C5.2, C6.2, C7.2, C8.2; also elsewhere on the board

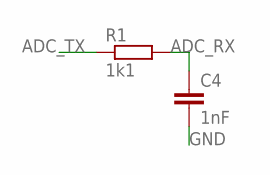
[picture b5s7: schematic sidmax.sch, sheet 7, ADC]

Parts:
C4: 1nF; C0402
R1: 1k1; R0402

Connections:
ADC_RX: C4.1, R1.2; also elsewhere on the board
ADC_TX: R1.1; also elsewhere on the board
GND: C4.2; also elsewhere on the board

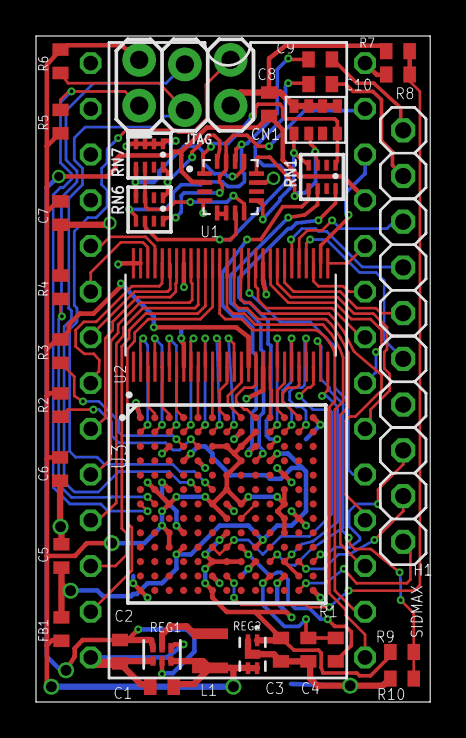
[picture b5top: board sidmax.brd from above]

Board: 4 copper layers, 21.9 x 37.0 mm, 37 parts (0 on the bottom side), 83 nets.
